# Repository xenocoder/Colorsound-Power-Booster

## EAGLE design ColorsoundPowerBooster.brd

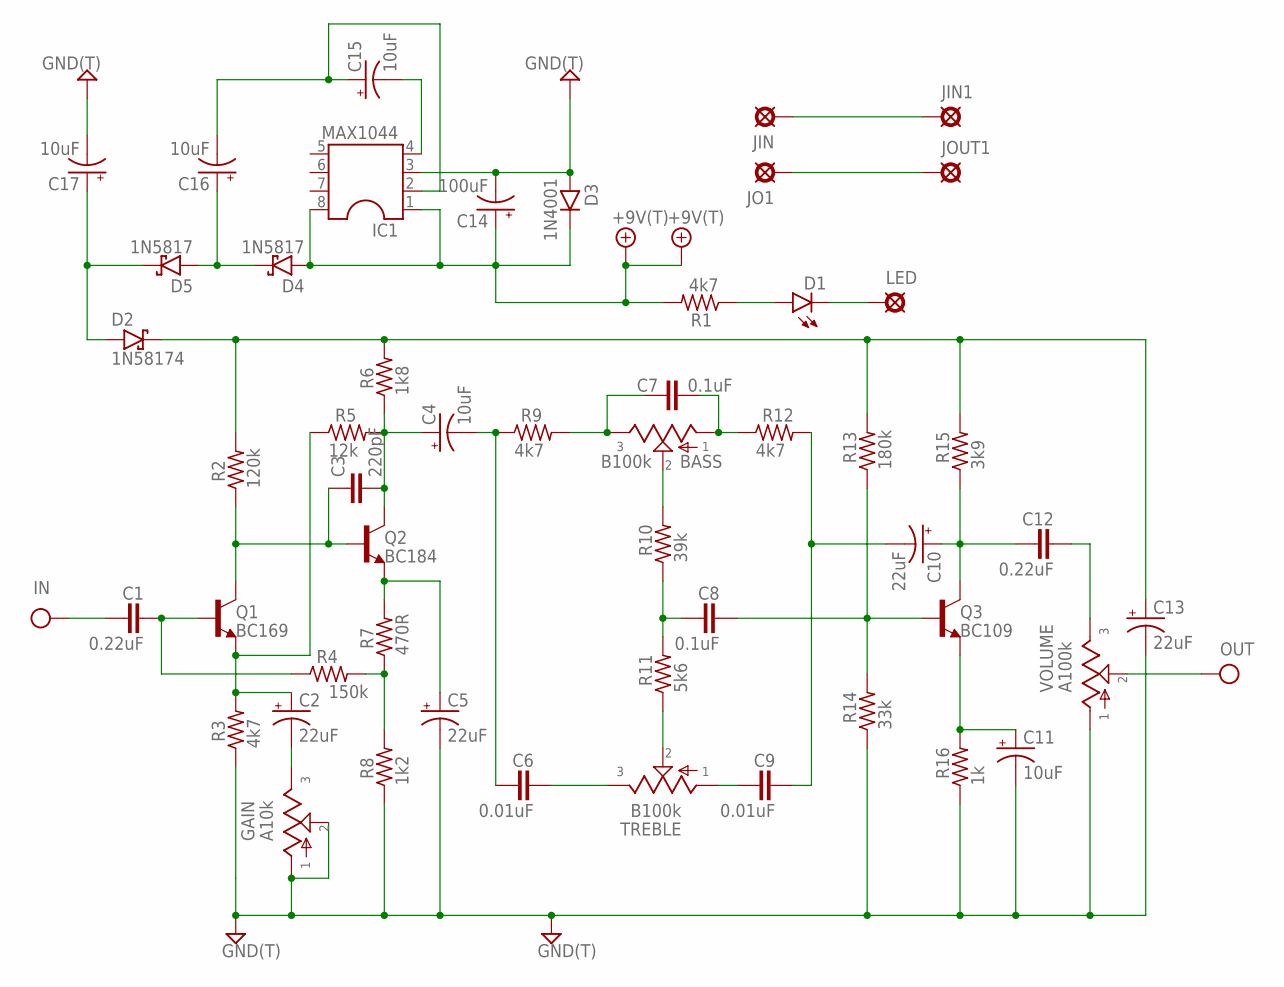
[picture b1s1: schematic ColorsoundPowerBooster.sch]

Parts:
+9V, +9V1: +9V(T); SQUARE
BASS: B100k; 16MM
C1, C12: 0.22uF; 072X025
C2, C5, C10, C13: 22uF; 050_020_1
C3: 220pF; 050X030_025
C4, C11, C15, C16, C17: 10uF; 050_020_1
C6, C9: 0.01uF; 072X025
C7, C8: 0.1uF; 072X025
C14: 100uF; 080_035_1
D1: LED; LED3MM
D2: 1N58174; DO41-4
D3: 1N4001; DO41-3
D4, D5: 1N5817; DO41-3
G, G6: GND(T); SQUARE
GAIN: A10k; 16MM
IC1: MAX1044; DIL08
IN: IN(T); SQUARE
JIG: GND(T); SQUARE
JIN, JIN1: PAD; SQUARE
JO1: PAD; SQUARE
JOG: GND(T); SQUARE
JOUT1: PAD; SQUARE
LED: PAD; SQUARE
OUT: OUT(T); SQUARE
Q1: BC169; TO92-
Q2: BC184; TO92-
Q3: BC109; TO92-
R1, R3, R9, R12: 4k7; R0207/3
R2: 120k; R0207/3
R4: 150k; R0207/3
R5: 12k; R0207/3
R6: 1k8; R0207/3
R7: 470R; R0207/3
R8: 1k2; R0207/3
R10: 39k; R0207/3
R11: 5k6; R0207/3
R13: 180k; R0207/3
R14: 33k; R0207/3
R15: 3k9; R0207/3
R16: 1k; R0207/3
TREBLE: B100k; 16MM
VOLUME: A100k; 16MM

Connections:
+9V: +9V.1, +9V1.1, C14.+, D3.C, D4.A, IC1.1, IC1.8, R1.2
GND: C5.-, C11.-, C13.-, C14.-, C17.-, D3.A, G.1, G6.1, GAIN.1, GAIN.2, IC1.3, JIG.1, JOG.1, R3.1, R8.1, R14.1, R16.1, VOLUME.1
IN: C1.1, IN.1
unnamed: C4.-, C6.1, R9.1
unnamed: C6.2, TREBLE.3
unnamed: C1.2, Q1.2 (B), R4.1
unnamed: C2.+, Q1.1 (E), R3.2, R5.1
unnamed: C2.-, GAIN.3
unnamed: C3.1, Q1.3 (C), Q2.2 (B), R2.1
unnamed: C3.2, C4.+, Q2.3 (C), R5.2, R6.1
unnamed: C5.+, Q2.1 (E), R7.2
unnamed: R4.2, R7.1, R8.2
unnamed: C13.+, D2.C, R2.2, R6.2, R13.2, R15.2
unnamed: R11.1, TREBLE.2
unnamed: C8.1, R10.1, R11.2
unnamed: BASS.2, R10.2
unnamed: C9.2, C10.-, R12.2
unnamed: C8.2, Q3.2 (B), R13.1, R14.2
unnamed: C9.1, TREBLE.1
unnamed: C10.+, C12.1, Q3.3 (C), R15.1
unnamed: C11.+, Q3.1 (E), R16.2
unnamed: D1.A, R1.1
unnamed: D1.K (C), LED.1
unnamed: C12.2, VOLUME.3
unnamed: JIN.1, JIN1.1
unnamed: C15.-, IC1.4
unnamed: C15.+, C16.-, IC1.2
unnamed: C16.+, D4.C, D5.A
unnamed: C17.+, D2.A, D5.C
unnamed: JO1.1, JOUT1.1
unnamed: BASS.3, C7.1, R9.2
unnamed: BASS.1, C7.2, R12.1
OUT: OUT.1, VOLUME.2

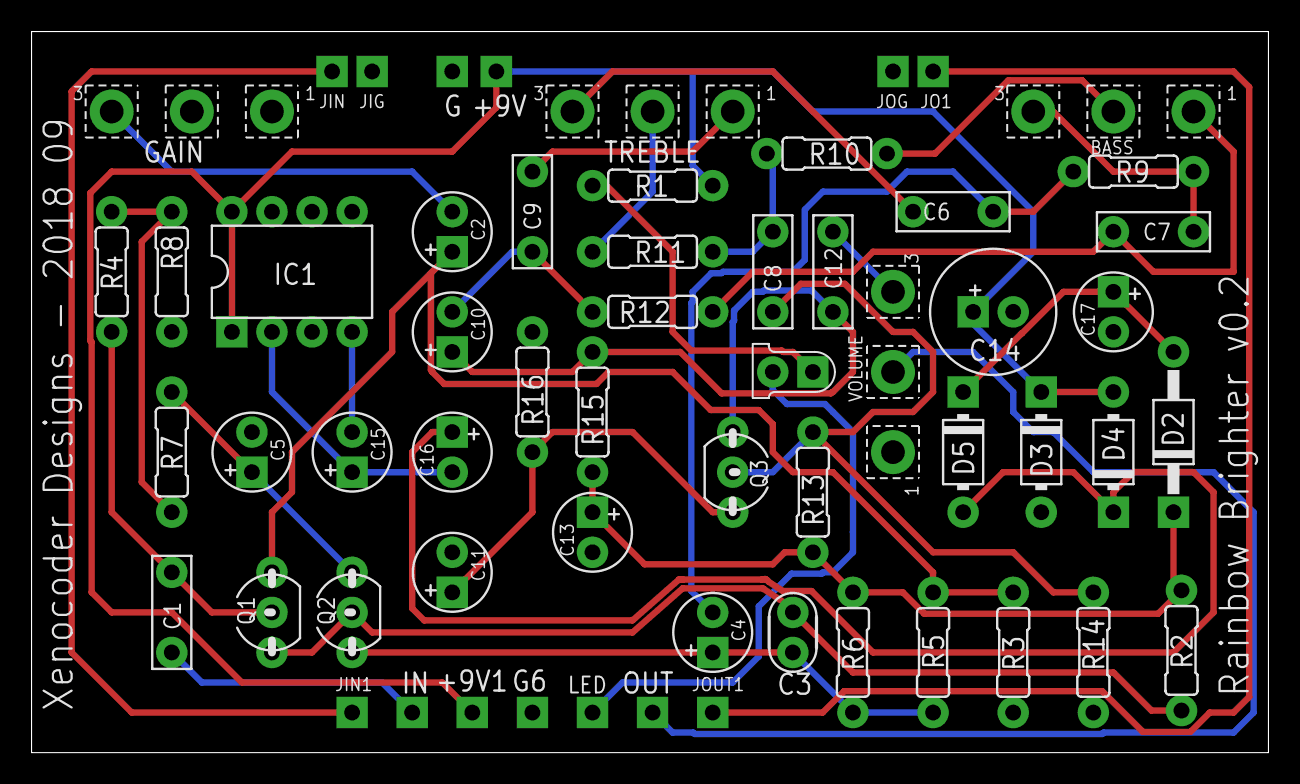
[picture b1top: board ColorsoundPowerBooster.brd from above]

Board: 2 copper layers, 78.4 x 45.7 mm, 59 parts (0 on the bottom side), 33 nets.

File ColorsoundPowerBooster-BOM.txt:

Partlist exported from /Users/evanhowell/git/Colorsound Power Booster/ColorsoundPowerBooster.sch at 10/18/18 6:27 PM

Part   Value   Device       Package     Description        
+9V    +9V(T)  +9V(T)       SQUARE      +9V Voltage Supply 
+9V1   +9V(T)  +9V(T)       SQUARE      +9V Voltage Supply 
BASS   B100k   POT16MM      16MM        Potentiometers     
C1     0.22uF  072X0252     072X025     1000pF - 0.47uF    
C2     22uF    0501         050_020_1   0.22 - 100uF       
C3     220pF   050X030_0251 050X030_025 47 - 120pF         
C4     10uF    0501         050_020_1   0.22 - 100uF       
C5     22uF    0501         050_020_1   0.22 - 100uF       
C6     0.01uF  072X0252     072X025     1000pF - 0.47uF    
C7     0.1uF   072X0252     072X025     1000pF - 0.47uF    
C8     0.1uF   072X0252     072X025     1000pF - 0.47uF    
C9     0.01uF  072X0252     072X025     1000pF - 0.47uF    
C10    22uF    0501         050_020_1   0.22 - 100uF       
C11    10uF    0501         050_020_1   0.22 - 100uF       
C12    0.22uF  072X0252     072X025     1000pF - 0.47uF    
C13    22uF    0501         050_020_1   0.22 - 100uF       
C14    100uF   0801         080_035_1   47 - 470uF         
C15    10uF    0501         050_020_1   0.22 - 100uF       
C16    10uF    0501         050_020_1   0.22 - 100uF       
C17    10uF    0501         050_020_1   0.22 - 100uF       
D1     LED     LED3MM       LED3MM                         
D2     1N58174 1N58174      DO41-4                         
D3     1N4001  1N400X.3     DO41-3      Rectifier Diodes   
D4     1N5817  1N5817       DO41-3                         
D5     1N5817  1N5817       DO41-3                         
G      GND(T)  GND(T)       SQUARE      Ground             
G6     GND(T)  GND(T)       SQUARE      Ground             
GAIN   A10k    POT16MM      16MM        Potentiometers     
IC1    MAX1044 MAX1044      DIL08                          
IN     IN(T)   IN(T)        SQUARE      Input              
JIG    GND(T)  GND(T)       SQUARE      Ground             
JIN            PAD          SQUARE      PAD                
JIN1           PAD          SQUARE      PAD                
JO1            PAD          SQUARE      PAD                
JOG    GND(T)  GND(T)       SQUARE      Ground             
JOUT1          PAD          SQUARE      PAD                
LED            PAD          SQUARE      PAD                
OUT    OUT(T)  OUT(T)       SQUARE      Output             
Q1     BC169   BC109        TO92-                          
Q2     BC184   BC109        TO92-                          
Q3     BC109   BC109        TO92-                          
R1     4k7     6MM.3        R0207/3     6mm Resistors      
R2     120k    6MM.3        R0207/3     6mm Resistors      
R3     4k7     6MM.3        R0207/3     6mm Resistors      
R4     150k    6MM.3        R0207/3     6mm Resistors      
R5     12k     6MM.3        R0207/3     6mm Resistors      
R6     1k8     6MM.3        R0207/3     6mm Resistors      
R7     470R    6MM.3        R0207/3     6mm Resistors      
R8     1k2     6MM.3        R0207/3     6mm Resistors      
R9     4k7     6MM.3        R0207/3     6mm Resistors      
R10    39k     6MM.3        R0207/3     6mm Resistors      
R11    5k6     6MM.3        R0207/3     6mm Resistors      
R12    4k7     6MM.3        R0207/3     6mm Resistors      
R13    180k    6MM.3        R0207/3     6mm Resistors      
R14    33k     6MM.3        R0207/3     6mm Resistors      
R15    3k9     6MM.3        R0207/3     6mm Resistors      
R16    1k      6MM.3        R0207/3     6mm Resistors      
TREBLE B100k   POT16MM      16MM        Potentiometers     
VOLUME A100k   POT16MM      16MM        Potentiometers

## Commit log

2018-08-24 First commit for new board
2018-09-06 Updated Partslist
2018-10-19 Updated to Version 1.1 to fix Gain and Bass pot wire inversion
